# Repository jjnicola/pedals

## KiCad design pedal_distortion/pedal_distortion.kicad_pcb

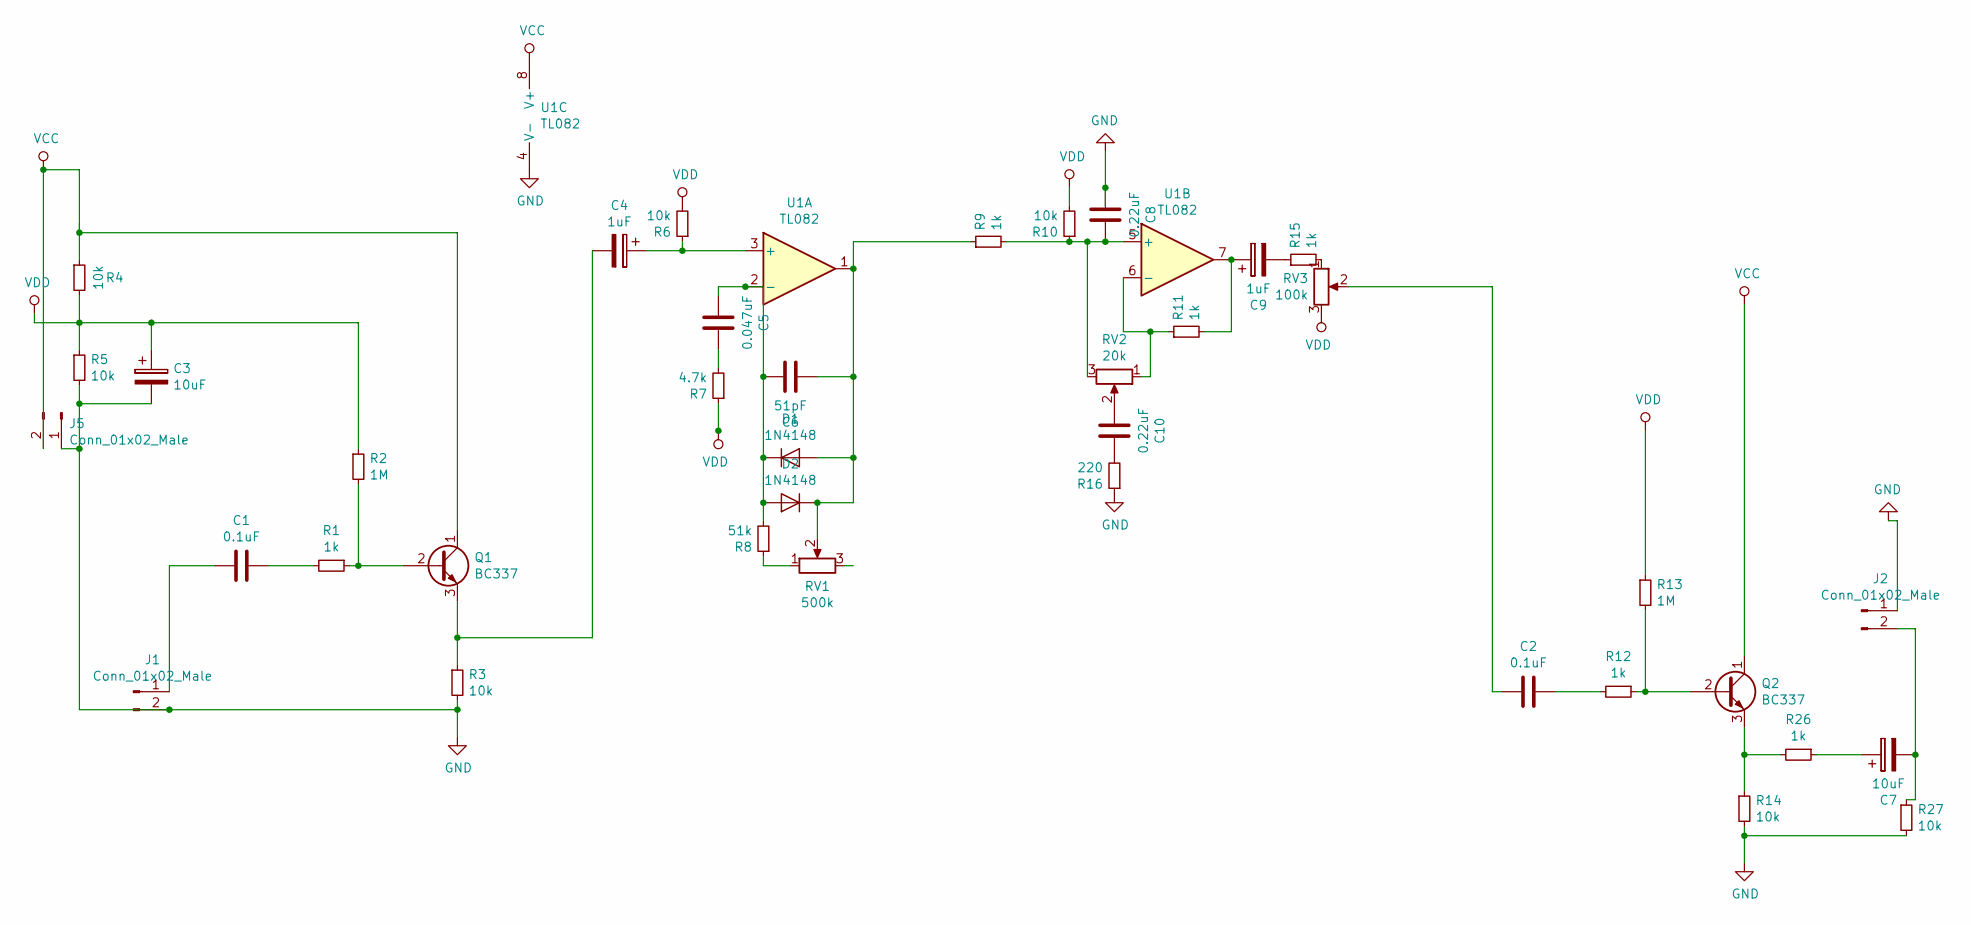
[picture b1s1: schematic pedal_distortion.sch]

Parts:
C1, C2: 0.1uF; C_Radial_D5.0mm_H7.0mm_P2.00mm
C3, C7: 10uF; CP_Radial_D5.0mm_P2.50mm
C4, C9: 1uF; CP_Radial_D5.0mm_P2.50mm
C5: 0.047uF; C_Radial_D5.0mm_H7.0mm_P2.00mm
C6: 51pF; C_Radial_D5.0mm_H7.0mm_P2.00mm
C8, C10: 0.22uF; C_Radial_D5.0mm_H7.0mm_P2.00mm
D1, D2: 1N4148; D_DO-35_SOD27_P7.62mm_Horizontal
J1, J2, J5: Conn_01x02_Male; SolderWirePad_1x02_P3.81mm_Drill0.8mm
Q1, Q2: BC337; TO-92_Inline
R1, R9, R11, R12, R15, R26: 1k; R_Axial_DIN0207_L6.3mm_D2.5mm_P10.16mm_Horizontal
R2, R13: 1M; R_Axial_DIN0207_L6.3mm_D2.5mm_P10.16mm_Horizontal
R3, R4, R5, R6, R10, R14, R27: 10k; R_Axial_DIN0207_L6.3mm_D2.5mm_P10.16mm_Horizontal
R7: 4.7k; R_Axial_DIN0207_L6.3mm_D2.5mm_P10.16mm_Horizontal
R8: 51k; R_Axial_DIN0207_L6.3mm_D2.5mm_P10.16mm_Horizontal
R16: 220; R_Axial_DIN0207_L6.3mm_D2.5mm_P10.16mm_Horizontal
RV1: 500k; Potentiometer_Alps_RK097_Single_Horizontal
RV2: 20k; Potentiometer_Alps_RK097_Single_Horizontal
RV3: 100k; Potentiometer_Alps_RK097_Single_Horizontal
U1: TL082; DIP-8_W7.62mm_LongPads

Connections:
unnamed: C1.1, R1.2
unnamed: C1.2, J1.1
unnamed: C2.1, R12.2
unnamed: C2.2, RV3.2
unnamed: C4.1, R6.1, U1.3 (+)
unnamed: C4.2, Q1.3 (E), R3.1
unnamed: C5.1, R7.2
unnamed: C5.2, C6.1, D1.1 (K), D2.2 (A), R8.2, U1.2 (-)
unnamed: C6.2, D1.2 (A), D2.1 (K), R9.1, RV1.2, U1.1
unnamed: C7.1, R26.1
unnamed: C7.2, J2.2, R27.1
unnamed: C8.1, R9.2, R10.1, RV2.3, U1.5 (+)
unnamed: C9.1, R11.2, U1.7
unnamed: C9.2, R15.1
unnamed: C10.1, R16.2
unnamed: C10.2, RV2.2
unnamed: Q1.2 (B), R1.1, R2.2
unnamed: Q2.2 (B), R12.1, R13.2
unnamed: Q2.3 (E), R14.1, R26.2
unnamed: R8.1, RV1.1
unnamed: R11.1, RV2.1, U1.6 (-)
unnamed: R15.2, RV3.1
VCC: J5.2, Q1.1 (C), Q2.1 (C), R4.1, U1.8 (V+)

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
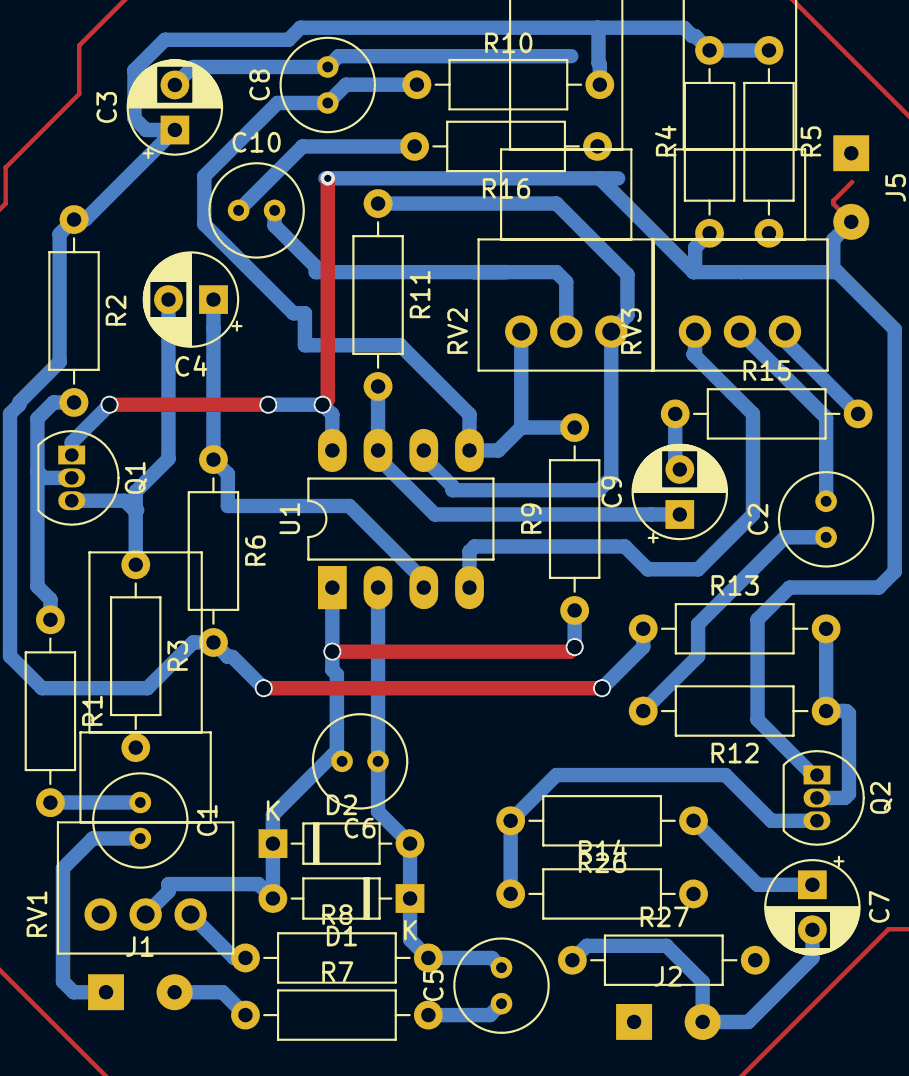
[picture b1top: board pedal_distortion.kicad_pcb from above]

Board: 2 copper layers, 39 parts (0 on the bottom side), 25 nets.

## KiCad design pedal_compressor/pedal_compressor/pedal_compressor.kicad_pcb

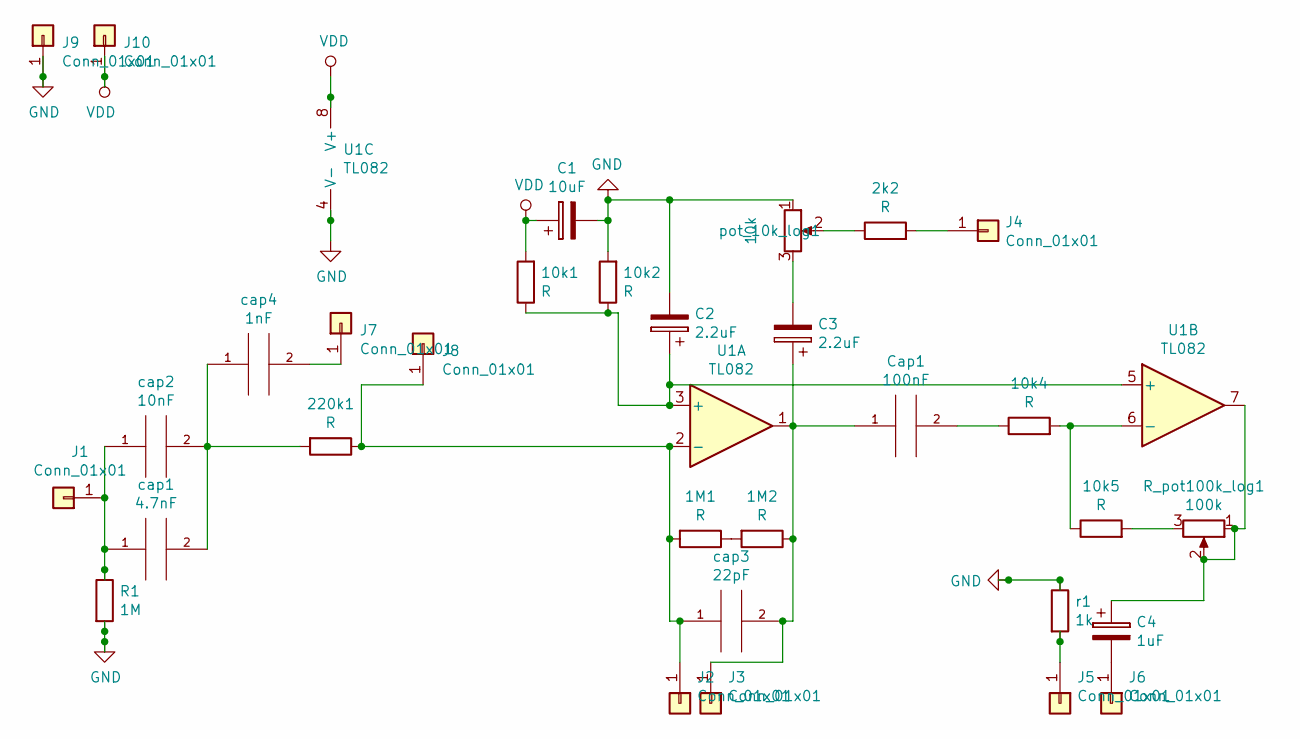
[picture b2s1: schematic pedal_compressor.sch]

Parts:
1M1, 1M2, 2k2, 10k1, 10k2, 10k4, 10k5, 220k1: R; R_Axial_DIN0207_L6.3mm_D2.5mm_P10.16mm_Horizontal
C1: 10uF; CP_Radial_D5.0mm_P2.00mm
C2, C3: 2.2uF; CP_Radial_D5.0mm_P2.00mm
C4: 1uF; CP_Radial_D5.0mm_P2.00mm
Cap1: 100nF; C_Disc_D4.3mm_W1.9mm_P5.00mm
J1, J2, J3, J4, J5, J6, J7, J8, J9, J10: Conn_01x01; SolderWirePad_1x01_Drill1.2mm
R1: 1M; R_Axial_DIN0207_L6.3mm_D2.5mm_P10.16mm_Horizontal
R_pot100k_log1: 100k; Potentiometer_Piher_PC-16_Single_Vertical
U1: TL082; DIP-8_W7.62mm_LongPads
cap1: 4.7nF; C_Disc_D4.3mm_W1.9mm_P5.00mm
cap2: 10nF; C_Disc_D4.3mm_W1.9mm_P5.00mm
cap3: 22pF; C_Disc_D4.3mm_W1.9mm_P5.00mm
cap4: 1nF; C_Disc_D4.3mm_W1.9mm_P5.00mm
pot_10k_log1: 10k; Potentiometer_Piher_PC-16_Single_Vertical
r1: 1k; R_Axial_DIN0207_L6.3mm_D2.5mm_P10.16mm_Horizontal

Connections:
GND: 10k2.2, C1.2, C2.2, J9.1, R1.2, U1.4 (V-), pot_10k_log1.1, r1.1
unnamed: 1M1.1, 1M2.2
unnamed: 1M1.2, 220k1.1, J2.1, J8.1, U1.2 (-), cap3.1
unnamed: 1M2.1, C3.1, Cap1.1, J3.1, U1.1, cap3.2
unnamed: 2k2.1, pot_10k_log1.2
unnamed: 2k2.2, J4.1
unnamed: 10k1.1, 10k2.1, C2.1, U1.3 (+), U1.5 (+)
unnamed: 10k4.1, Cap1.2
unnamed: 10k4.2, 10k5.1, U1.6 (-)
unnamed: 10k5.2, R_pot100k_log1.3
unnamed: 220k1.2, cap1.2, cap2.2, cap4.1
unnamed: C3.2, pot_10k_log1.3
unnamed: C4.1, R_pot100k_log1.1, R_pot100k_log1.2, U1.7
unnamed: C4.2, J6.1
unnamed: J1.1, R1.1, cap1.1, cap2.1
unnamed: J5.1, r1.2
unnamed: J7.1, cap4.2
VDD: 10k1.2, C1.1, J10.1, U1.8 (V+)

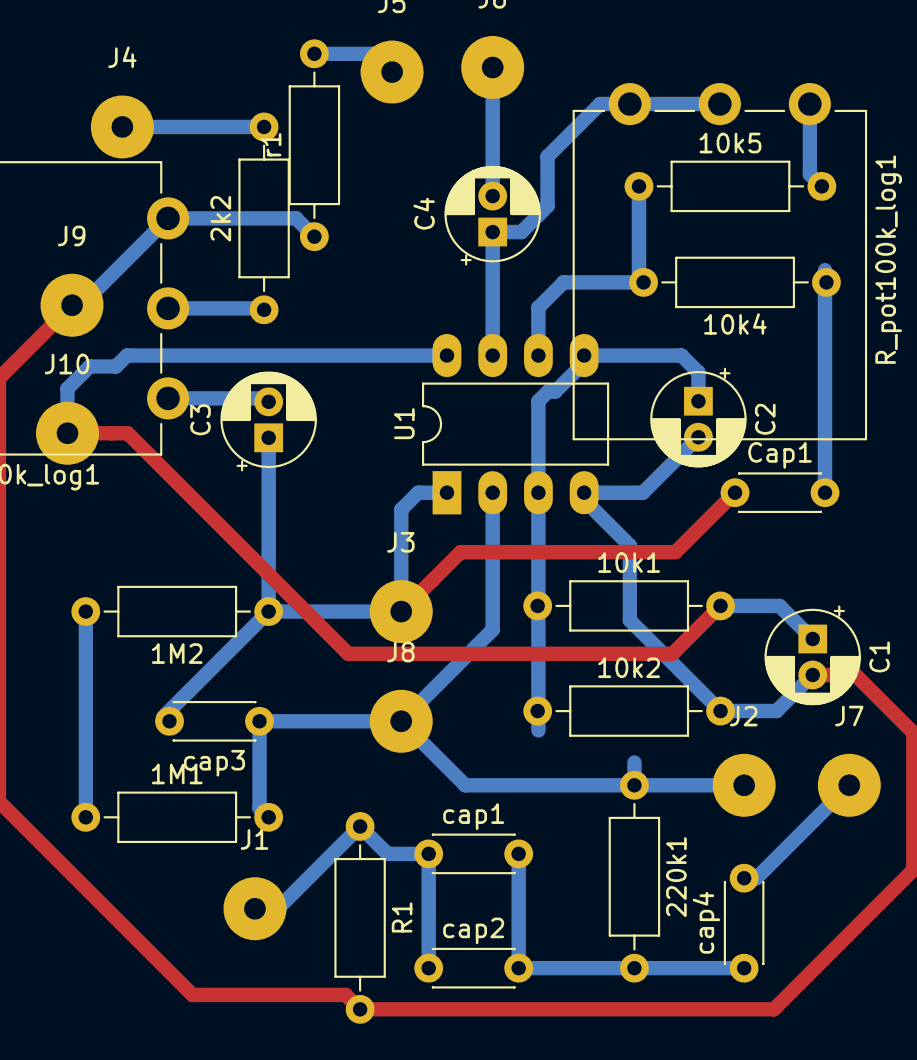
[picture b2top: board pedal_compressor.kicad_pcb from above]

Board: 2 copper layers, 32 parts (0 on the bottom side), 18 nets.

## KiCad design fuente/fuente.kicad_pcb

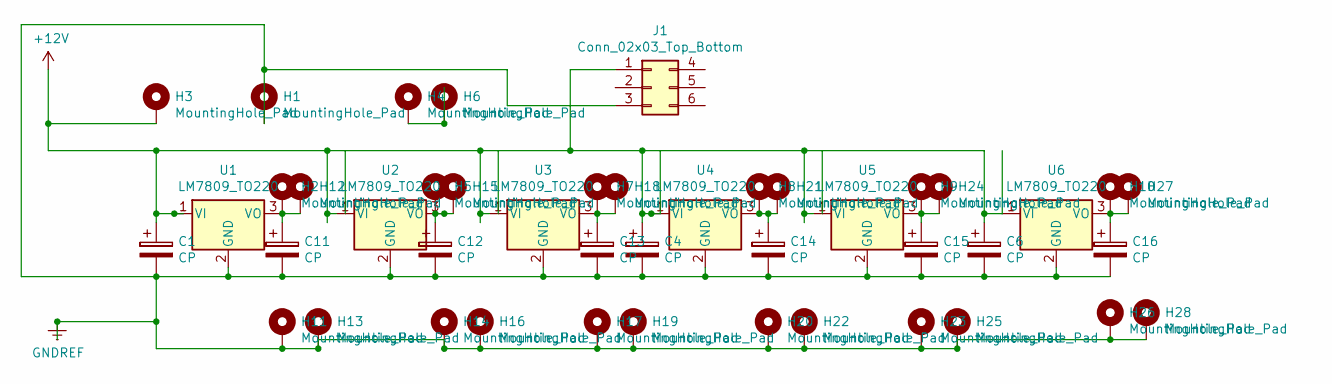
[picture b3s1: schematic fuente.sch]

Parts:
C1, C4, C6, C11, C12, C13, C14, C15, C16: CP; CP_Radial_D10.0mm_P2.50mm
H1, H2, H3, H4, H5, H6, H7, H8, H9, H10, H11, H12, H13, H14, H15, H16, H17, H18, H19, H20, H21, H22, H23, H24, H25, H26, H27, H28: MountingHole_Pad; MountingHole_3.5mm_Pad_Via
J1: Conn_02x03_Top_Bottom; IDC-Header_2x03_P2.54mm_Horizontal
U1, U2, U3, U4, U5, U6: LM7809_TO220; TO-220-3_Vertical

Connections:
+12V: C1.1, C4.1, C6.1, H3.1, J1.1, U1.1 (VI), U2.1 (VI), U3.1 (VI), U4.1 (VI), U5.1 (VI), U6.1 (VI)
GNDREF: C1.2, C4.2, C6.2, C11.2, C12.2, C13.2, C14.2, C15.2, C16.2, H1.1, H11.1, H13.1, H14.1, H16.1, H17.1, H19.1, H20.1, H22.1, H23.1, H25.1, H26.1, H28.1, J1.3, U1.2 (GND), U2.2 (GND), U3.2 (GND), U4.2 (GND), U5.2 (GND), U6.2 (GND)
unnamed: C11.1, H2.1, H12.1, U1.3 (VO)
unnamed: C12.1, H5.1, H15.1, U2.3 (VO)
unnamed: C13.1, H7.1, H18.1, U3.3 (VO)
unnamed: C14.1, H8.1, H21.1, U4.3 (VO)
unnamed: C15.1, H9.1, H24.1, U5.3 (VO)
unnamed: C16.1, H10.1, H27.1, U6.3 (VO)
unnamed: H4.1, H6.1

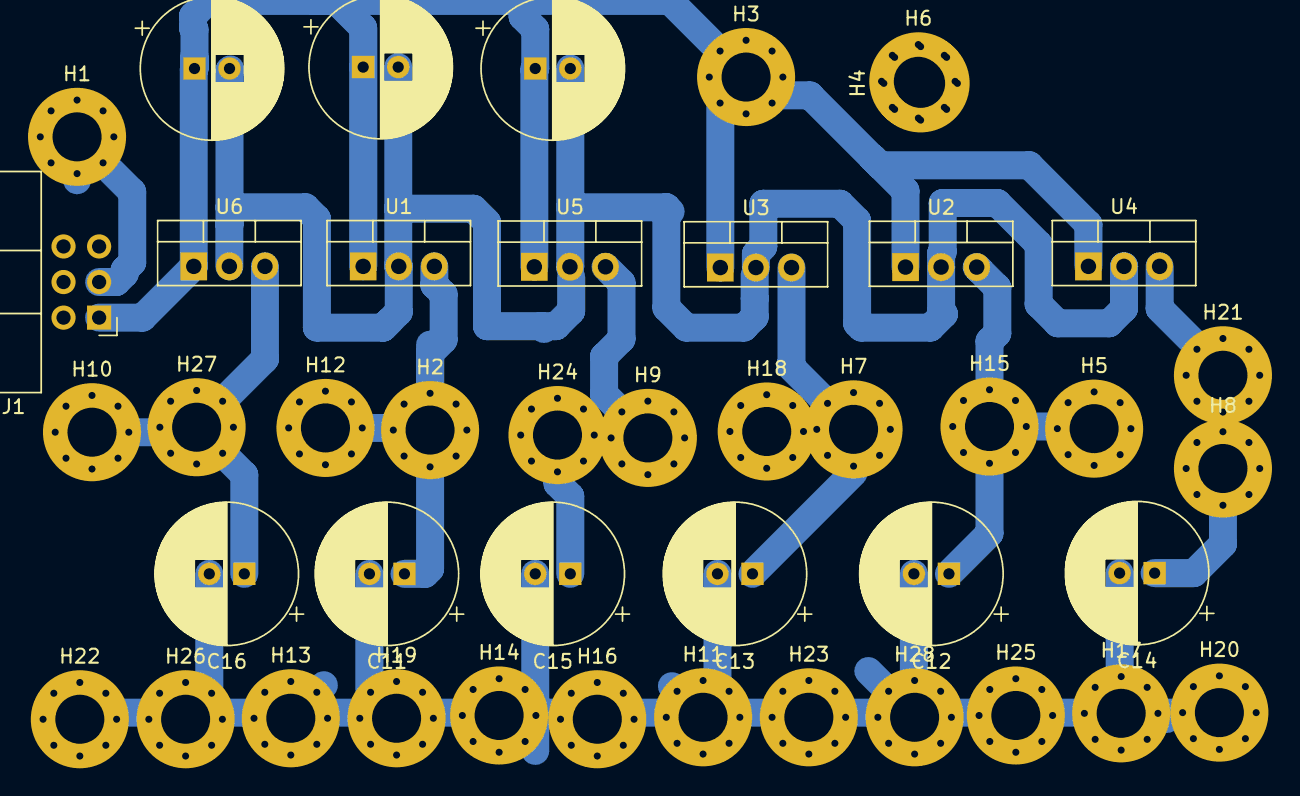
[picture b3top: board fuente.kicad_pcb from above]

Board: 2 copper layers, 44 parts (0 on the bottom side), 9 nets.

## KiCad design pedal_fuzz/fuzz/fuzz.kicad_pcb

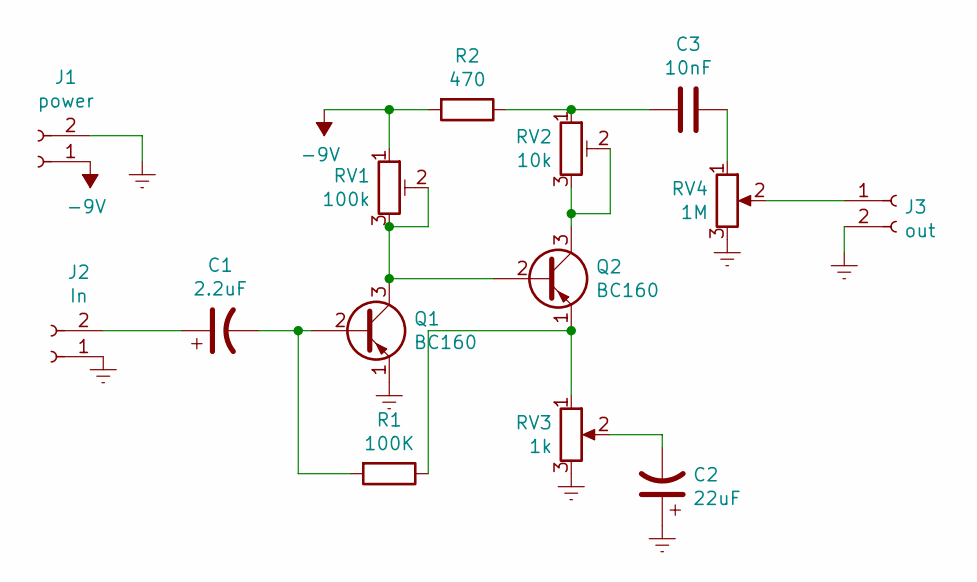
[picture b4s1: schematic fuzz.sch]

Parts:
C1: 2.2uF; CP_Radial_D4.0mm_P1.50mm
C2: 22uF; CP_Radial_D4.0mm_P1.50mm
C3: 10nF; C_Disc_D5.0mm_W2.5mm_P2.50mm
J1: power; SolderWirePad_1x02_P3.81mm_Drill1.2mm
J2: In; SolderWirePad_1x02_P3.81mm_Drill1.2mm
J3: out; SolderWirePad_1x02_P3.81mm_Drill1.2mm
Q1, Q2: BC160; TO-39-3
R1: 100K; R_Axial_DIN0207_L6.3mm_D2.5mm_P7.62mm_Horizontal
R2: 470; R_Axial_DIN0207_L6.3mm_D2.5mm_P7.62mm_Horizontal
RV1: 100k; Potentiometer_Bourns_3386F_Vertical
RV2: 10k; Potentiometer_Bourns_3386F_Vertical
RV3: 1k; Potentiometer_Piher_T-16H_Single_Horizontal
RV4: 1M; Potentiometer_Piher_T-16H_Single_Horizontal

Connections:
-9V: J1.1, R2.2, RV1.1
Earth: C2.1, J1.2, J2.1, J3.2, Q1.1 (E), RV3.3, RV4.3
unnamed: C1.1, J2.2
unnamed: C1.2, Q1.2 (B), R1.2
unnamed: C2.2, RV3.2
unnamed: C3.1, R2.1, RV2.1
unnamed: C3.2, RV4.1
unnamed: J3.1, RV4.2
unnamed: Q1.3 (C), Q2.2 (B), RV1.2, RV1.3
unnamed: Q2.1 (E), R1.1, RV3.1
unnamed: Q2.3 (C), RV2.2, RV2.3

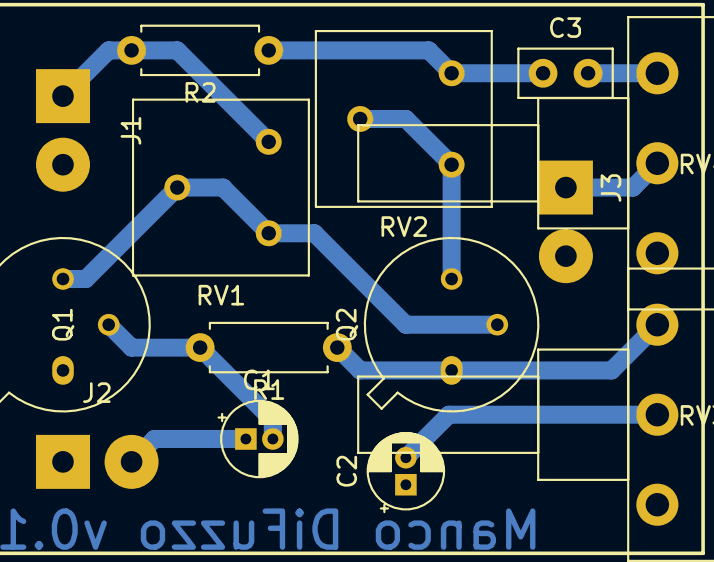
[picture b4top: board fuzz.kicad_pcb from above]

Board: 2 copper layers, 14 parts (0 on the bottom side), 11 nets.

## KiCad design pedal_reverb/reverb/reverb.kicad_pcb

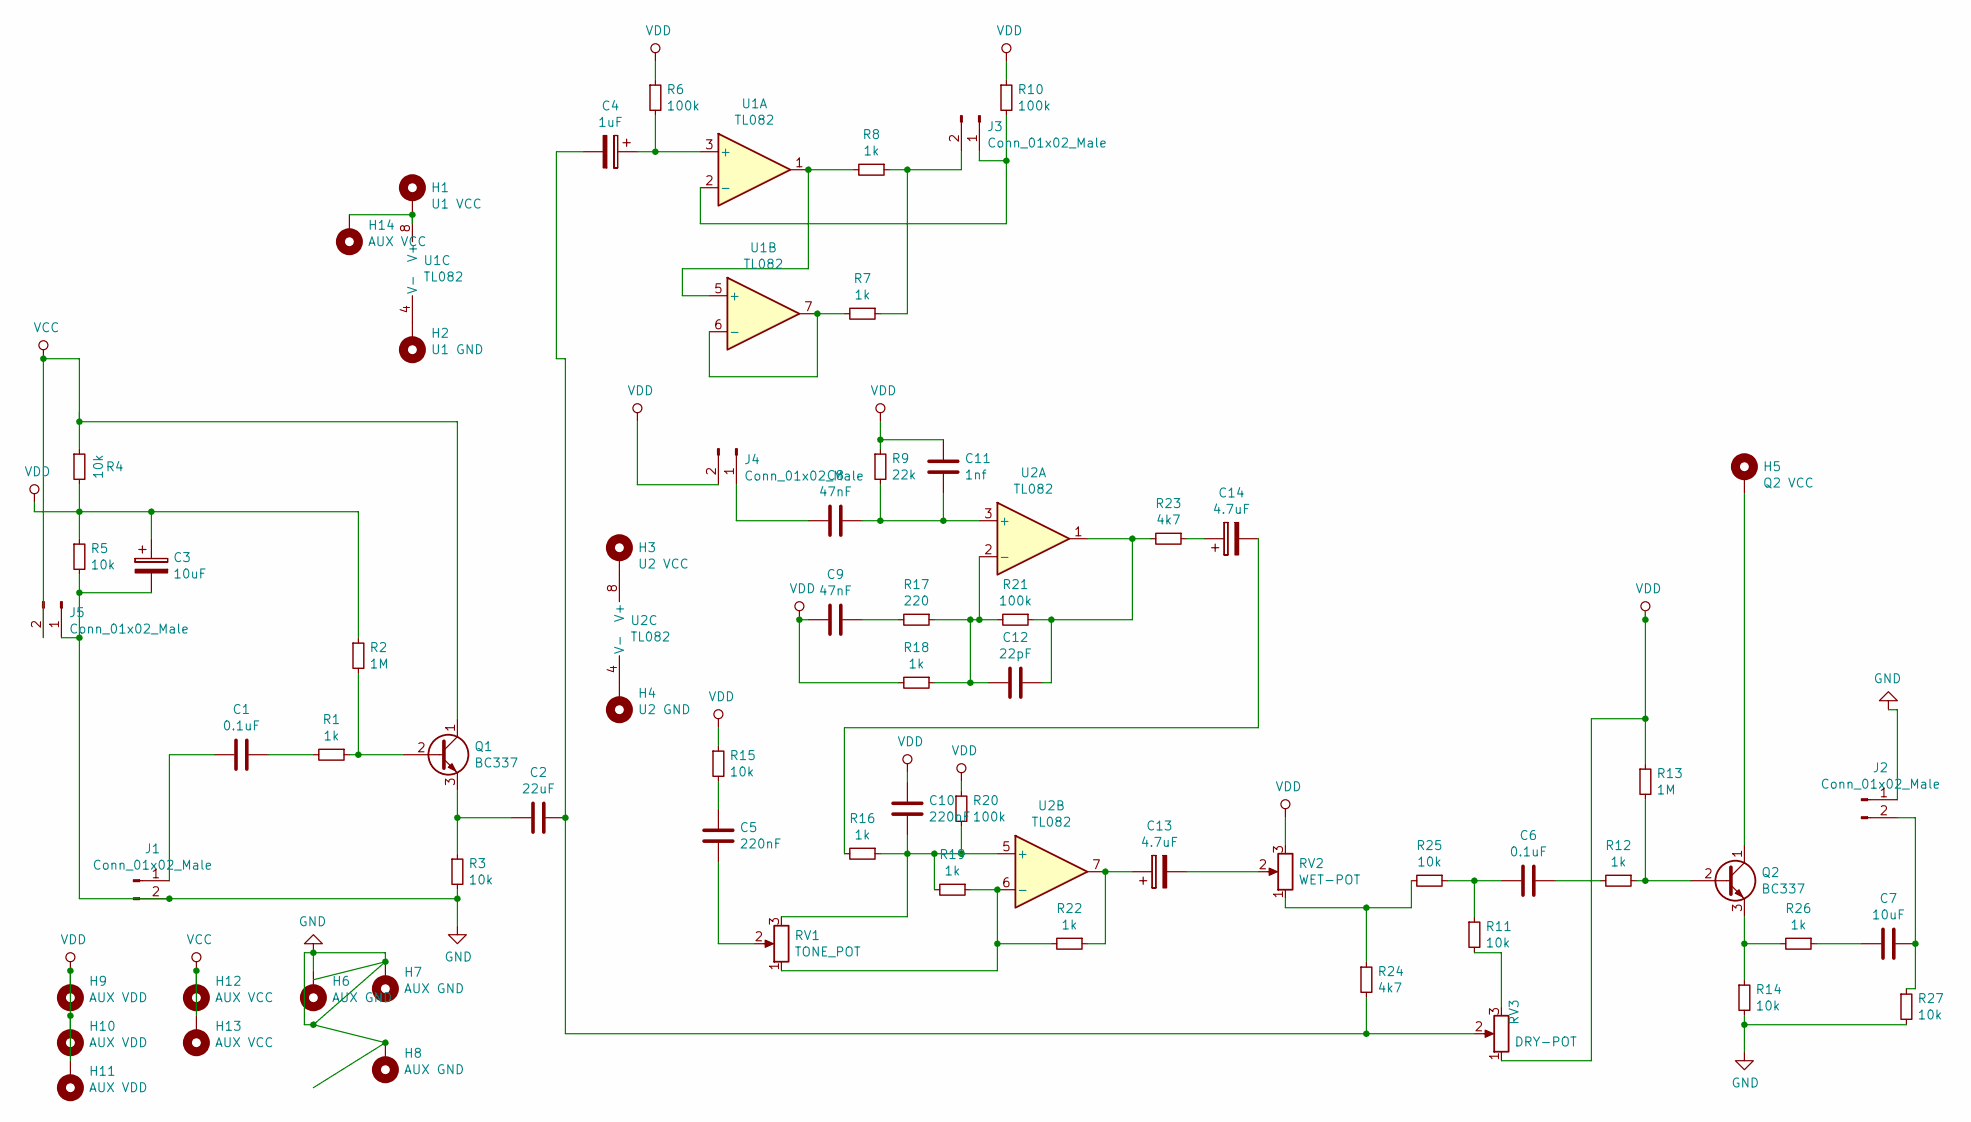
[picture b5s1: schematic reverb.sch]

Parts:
C1: 0.1uF; C_Rect_L7.0mm_W2.5mm_P5.00mm
C2: 22uF; C_Rect_L4.6mm_W3.0mm_P2.50mm_MKS02_FKP02
C3: 10uF; CP_Radial_D4.0mm_P1.50mm
C4: 1uF; CP_Radial_D4.0mm_P1.50mm
C5, C10: 220nF; C_Rect_L7.0mm_W2.0mm_P5.00mm
C6: 0.1uF; C_Disc_D3.0mm_W1.6mm_P2.50mm
C7: 10uF; C_Radial_D5.0mm_H11.0mm_P2.00mm
C8, C9: 47nF; C_Rect_L4.6mm_W3.0mm_P2.50mm_MKS02_FKP02
C11: 1nf; C_Disc_D3.0mm_W1.6mm_P2.50mm
C12: 22pF; C_Disc_D3.0mm_W1.6mm_P2.50mm
C13, C14: 4.7uF; CP_Radial_D4.0mm_P1.50mm
H1: U1 VCC; MountingHole_2.7mm_M2.5_Pad_Via
H2: U1 GND; MountingHole_2.7mm_M2.5_Pad_Via
H3: U2 VCC; MountingHole_2.7mm_M2.5_Pad_Via
H4: U2 GND; MountingHole_2.7mm_M2.5_Pad_Via
H5: Q2 VCC; MountingHole_2.7mm_M2.5_Pad_Via
H6, H7, H8: AUX GND; MountingHole_2.7mm_M2.5_Pad_Via
H9, H10, H11: AUX VDD; MountingHole_2.7mm_M2.5_Pad_Via
H12, H13, H14: AUX VCC; MountingHole_2.7mm_M2.5_Pad_Via
J1, J2, J3, J4, J5: Conn_01x02_Male; SolderWirePad_1x02_P3.81mm_Drill0.8mm
Q1, Q2: BC337; TO-92_Inline
R1, R7, R8, R12, R16, R18, R19, R22, R26: 1k; R_Axial_DIN0204_L3.6mm_D1.6mm_P5.08mm_Horizontal
R2, R13: 1M; R_Axial_DIN0204_L3.6mm_D1.6mm_P5.08mm_Horizontal
R3, R4, R5, R11, R14, R15, R25, R27: 10k; R_Axial_DIN0204_L3.6mm_D1.6mm_P5.08mm_Horizontal
R6, R10, R20, R21: 100k; R_Axial_DIN0204_L3.6mm_D1.6mm_P5.08mm_Horizontal
R9: 22k; R_Axial_DIN0204_L3.6mm_D1.6mm_P5.08mm_Horizontal
R17: 220; R_Axial_DIN0204_L3.6mm_D1.6mm_P5.08mm_Horizontal
R23, R24: 4k7; R_Axial_DIN0204_L3.6mm_D1.6mm_P5.08mm_Horizontal
RV1: TONE_POT; Potentiometer_Piher_T-16H_Single_Horizontal
RV2: WET-POT; Potentiometer_Piher_T-16H_Single_Horizontal
RV3: DRY-POT; Potentiometer_Piher_T-16H_Single_Horizontal
U1, U2: TL082; DIP-8_W7.62mm_Socket

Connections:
GND: C3.2, H6.1, H7.1, H8.1, J1.2, J2.1, J5.1, R3.2, R5.2, R14.2, R27.2
unnamed: C1.1, R1.2
unnamed: C1.2, J1.1
unnamed: C2.1, C4.2, R24.2, RV3.2
unnamed: C2.2, Q1.3 (E), R3.1
unnamed: C4.1, R6.2, U1.3 (+)
unnamed: C5.1, RV1.2
unnamed: C5.2, R15.2
unnamed: C6.1, R12.2
unnamed: C6.2, R11.1, R25.1
unnamed: C7.1, J2.2, R27.1
unnamed: C7.2, R26.1
unnamed: C8.2, J4.1
unnamed: C9.1, R17.2
unnamed: C10.1, R16.1, R19.2, R20.2, RV1.3, U2.5 (+)
unnamed: C8.1, C11.1, R9.2, U2.3 (+)
unnamed: C12.1, R21.1, R23.2, U2.1
unnamed: C12.2, R17.1, R18.1, R21.2, U2.2 (-)
unnamed: C13.1, R22.1, U2.7
unnamed: C13.2, RV2.2
unnamed: C14.1, R23.1
unnamed: C14.2, R16.2
unnamed: H1.1, H14.1, U1.8 (V+)
unnamed: H2.1, U1.4 (V-)
unnamed: H3.1, U2.8 (V+)
unnamed: H4.1, U2.4 (V-)
unnamed: H5.1, Q2.1 (C)
unnamed: J3.1, R10.2, U1.2 (-)
unnamed: J3.2, R7.1, R8.1
unnamed: Q1.2 (B), R1.1, R2.2
unnamed: Q2.2 (B), R12.1, R13.2
unnamed: Q2.3 (E), R14.1, R26.2
unnamed: R7.2, U1.6 (-), U1.7
unnamed: R8.2, U1.1, U1.5 (+)
unnamed: R11.2, RV3.3
unnamed: R19.1, R22.2, RV1.1, U2.6 (-)
unnamed: R24.1, R25.2, RV2.1
VCC: H12.1, H13.1, J5.2, Q1.1 (C), R4.1
VDD: C3.1, C9.2, C10.2, C11.2, H9.1, H10.1, H11.1, J4.2, R2.1, R4.2, R5.1, R6.1, R9.1, R10.1, R13.1, R15.1, R18.2, R20.1, RV2.3, RV3.1

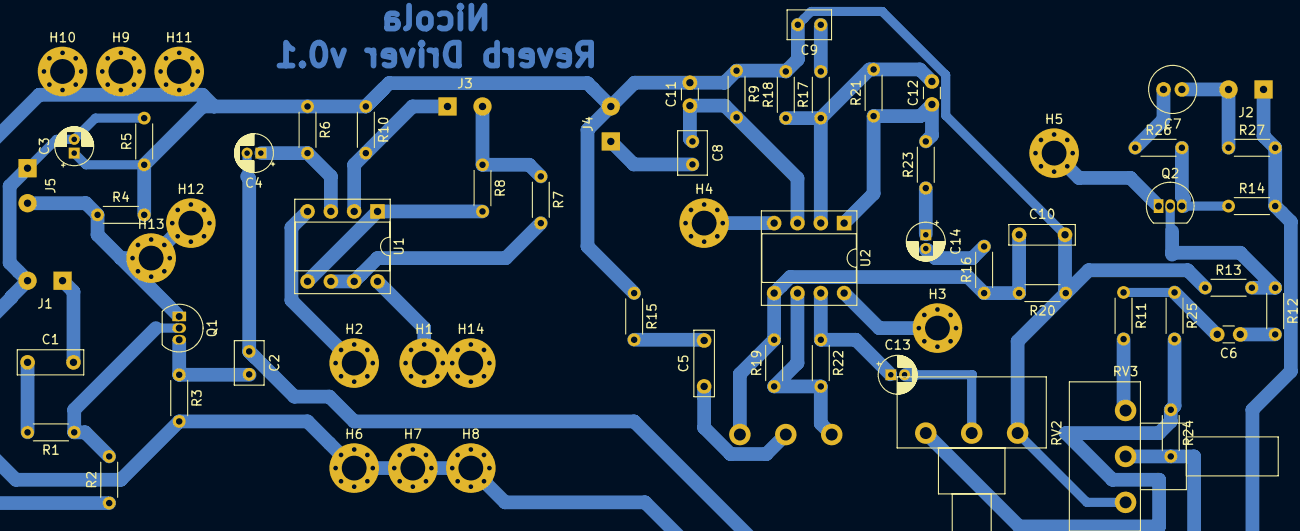
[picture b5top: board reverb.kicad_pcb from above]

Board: 2 copper layers, 67 parts (1 on the bottom side), 39 nets.

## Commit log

2021-04-24 Init commit
2021-06-14 Add pedals
